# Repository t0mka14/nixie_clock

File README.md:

# nixie_clock
6 digit nixie clock

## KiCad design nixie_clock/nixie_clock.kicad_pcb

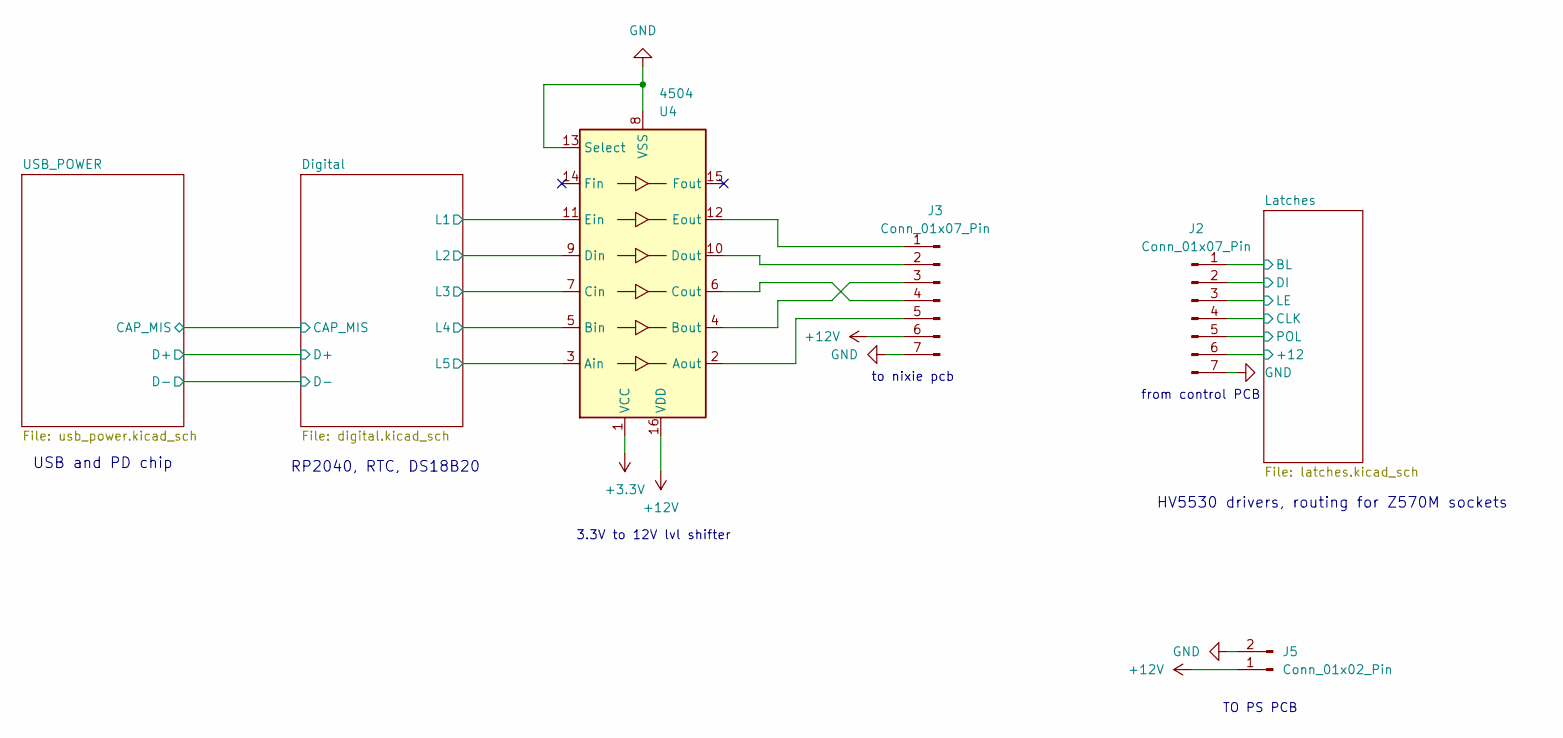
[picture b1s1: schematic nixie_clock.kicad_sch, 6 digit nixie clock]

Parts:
J2, J3: Conn_01x07_Pin; PinHeader_1x07_P2.54mm_Vertical
J5: Conn_01x02_Pin; PinHeader_1x02_P2.54mm_Vertical
U4: 4504; Texas_PDSO_G16

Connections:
+3.3V: U4.1 (VCC); also elsewhere on the board
+12V: J3.6, J5.1, U4.16 (VDD); also elsewhere on the board
/Digital/L1: U4.11 (Ein); also elsewhere on the board
/Digital/L2: U4.9 (Din); also elsewhere on the board
/Digital/L3: U4.7 (Cin); also elsewhere on the board
/Digital/L4: U4.5 (Bin); also elsewhere on the board
/Digital/L5: U4.3 (Ain); also elsewhere on the board
/Latches/+12: J2.6; also elsewhere on the board
/Latches/BL: J2.1; also elsewhere on the board
/Latches/CLK: J2.4; also elsewhere on the board
/Latches/DI: J2.2; also elsewhere on the board
/Latches/LE: J2.3; also elsewhere on the board
/Latches/POL: J2.5; also elsewhere on the board
GND: J2.7, J3.7, J5.2, U4.8 (VSS), U4.13 (Select); also elsewhere on the board
unnamed: J3.1, U4.12 (Eout)
unnamed: J3.2, U4.10 (Dout)
unnamed: J3.3, U4.4 (Bout)
unnamed: J3.4, U4.6 (Cout)
unnamed: J3.5, U4.2 (Aout)

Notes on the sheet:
to nixie pcb
USB and PD chip
TO PS PCB
RP2040, RTC, DS18B20
from control PCB
HV5530 drivers, routing for Z570M sockets
3.3V to 12V lvl shifter

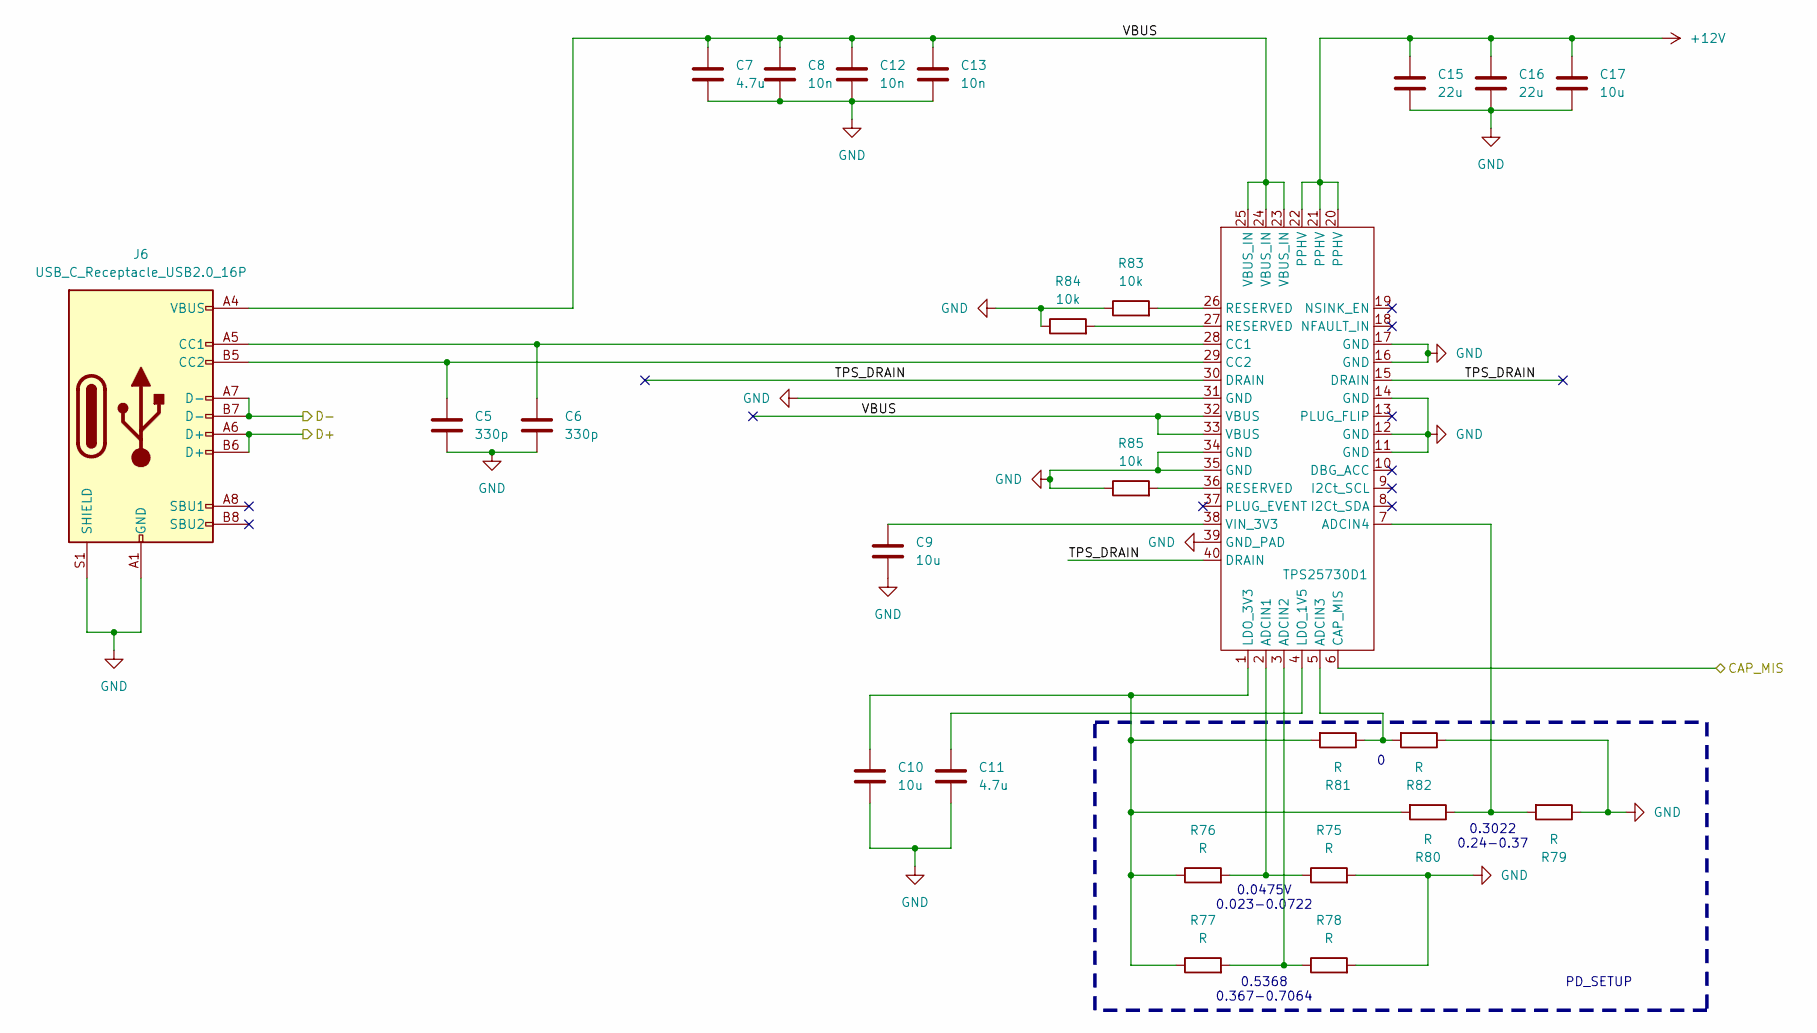
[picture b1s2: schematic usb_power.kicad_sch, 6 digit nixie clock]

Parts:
C5, C6: 330p; C_0603_1608Metric
C7, C11: 4.7u; C_0805_2012Metric
C8, C12, C13: 10n; C_0805_2012Metric
C9, C10, C17: 10u; C_0805_2012Metric
C15, C16: 22u; C_0805_2012Metric
J6: USB_C_Receptacle_USB2.0_16P; Conn_USB_C_Socket_Molex_2171790001
R75, R76, R77, R78, R79, R80, R81, R82: R; R_0805_2012Metric
R83, R84, R85: 10k; R_0805_2012Metric
TPS25730D1: IC_TPS25730D

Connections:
+12V: C15.1, C16.1, C17.1, TPS25730D1.20 (PPHV), TPS25730D1.21 (PPHV), TPS25730D1.22 (PPHV); also elsewhere on the board
/Digital/CAP_MIS: TPS25730D1.6 (CAP_MIS); also elsewhere on the board
/Digital/D+: J6.A6 (D+), J6.B6 (D+); also elsewhere on the board
/Digital/D-: J6.A7 (D-), J6.B7 (D-); also elsewhere on the board
/USB_POWER/TPS_DRAIN: TPS25730D1.15 (DRAIN), TPS25730D1.30 (DRAIN), TPS25730D1.40 (DRAIN)
/USB_POWER/VBUS: C7.1, C8.1, C12.1, C13.1, J6.A4 (VBUS), J6.A9 (VBUS), J6.B4 (VBUS), J6.B9 (VBUS), TPS25730D1.23 (VBUS_IN), TPS25730D1.24 (VBUS_IN), TPS25730D1.25 (VBUS_IN), TPS25730D1.32 (VBUS), TPS25730D1.33 (VBUS)
GND: C5.2, C6.2, C7.2, C8.2, C9.1, C10.2, C11.2, C12.2, C13.2, C15.2, C16.2, C17.2, J6.A1 (GND), J6.A12 (GND), J6.B1 (GND), J6.B12 (GND), J6.S1 (SHIELD), R75.2, R78.2, R79.1, R82.1, R83.1, R84.1, R85.1, TPS25730D1.11 (GND), TPS25730D1.12 (GND), TPS25730D1.14 (GND), TPS25730D1.16 (GND), TPS25730D1.17 (GND), TPS25730D1.31 (GND), TPS25730D1.34 (GND), TPS25730D1.35 (GND), TPS25730D1.39 (GND_PAD); also elsewhere on the board
unnamed: C6.1, J6.A5 (CC1), TPS25730D1.28 (CC1)
unnamed: C5.1, J6.B5 (CC2), TPS25730D1.29 (CC2)
unnamed: R83.2, TPS25730D1.26 (RESERVED)
unnamed: R84.2, TPS25730D1.27 (RESERVED)
unnamed: R85.2, TPS25730D1.36 (RESERVED)
unnamed: R75.1, R76.2, TPS25730D1.2 (ADCIN1)
unnamed: R77.2, R78.1, TPS25730D1.3 (ADCIN2)
unnamed: R81.1, R82.2, TPS25730D1.5 (ADCIN3)
unnamed: R79.2, R80.1, TPS25730D1.7 (ADCIN4)
unnamed: C11.1, TPS25730D1.4 (LDO_1V5)
unnamed: C10.1, R76.1, R77.1, R80.2, R81.2, TPS25730D1.1 (LDO_3V3)
unnamed: C9.2, TPS25730D1.38 (VIN_3V3)

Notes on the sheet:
PD_SETUP
0.5368 0.367-0.7064
0.3022 0.24-0.37
0.0475V 0.023-0.0722

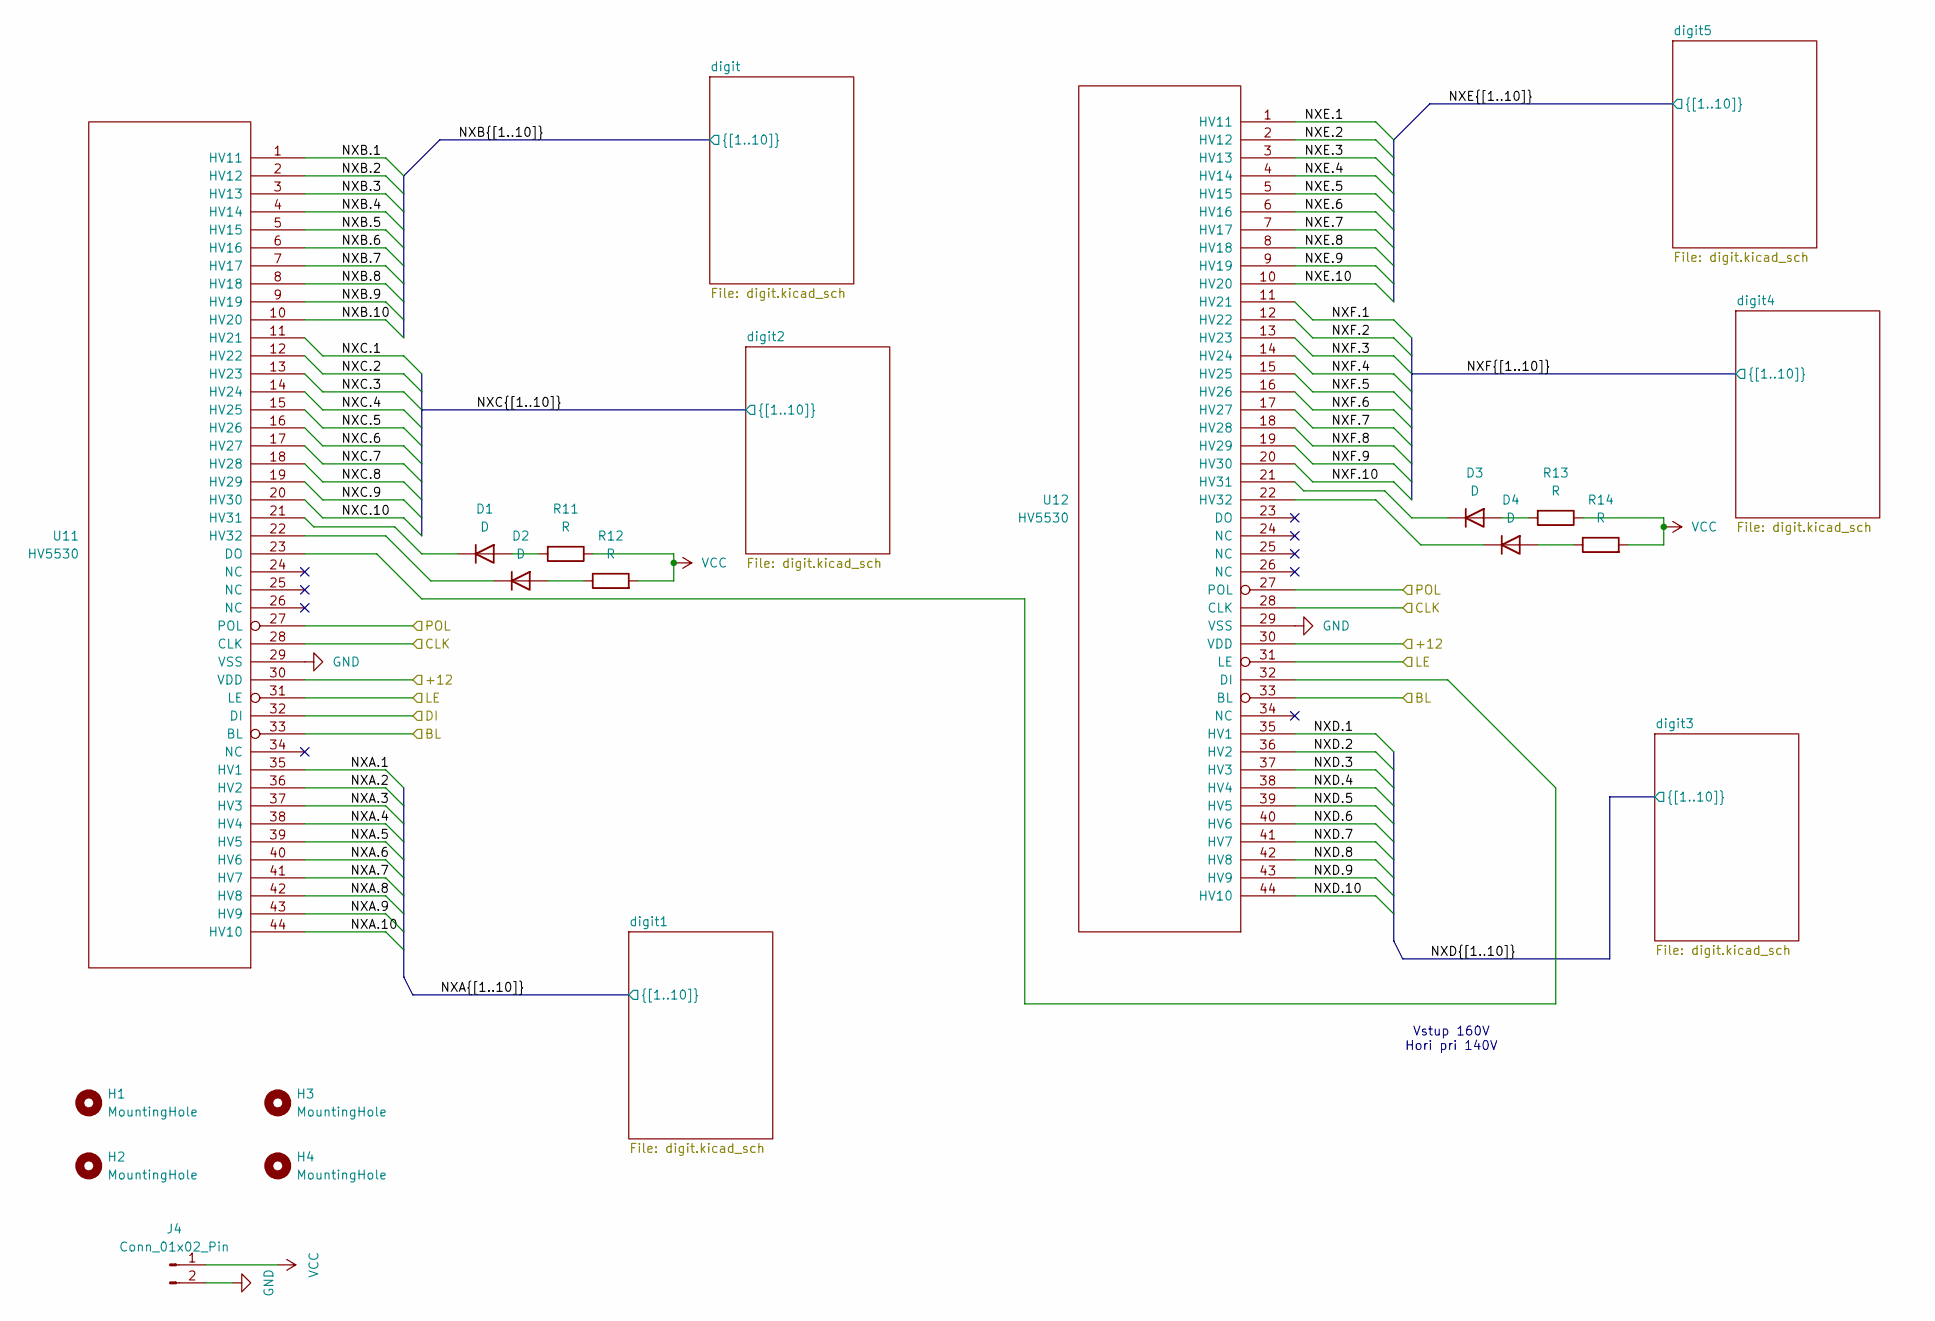
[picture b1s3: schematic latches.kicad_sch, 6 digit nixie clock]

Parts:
D1, D2, D3, D4: D; CP_Radial_D8.0mm_P5.00mm
H1, H2, H3, H4: MountingHole; MountingHole_3.2mm_M3
J4: Conn_01x02_Pin; PhoenixContact_MCV_1,5_2-G-3.5_1x02_P3.50mm_Vertical
R11, R12, R13, R14: R; R_1206_3216Metric
U11, U12: HV5530; PQFP-44_HV5530

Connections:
/Latches/+12: U11.30 (VDD), U12.30 (VDD); also elsewhere on the board
/Latches/BL: U11.33 (BL), U12.33 (BL); also elsewhere on the board
/Latches/CLK: U11.28 (CLK), U12.28 (CLK); also elsewhere on the board
/Latches/DI: U11.32 (DI); also elsewhere on the board
/Latches/LE: U11.31 (LE), U12.31 (LE); also elsewhere on the board
/Latches/NXA.1: U11.35 (HV1); also elsewhere on the board
/Latches/NXA.2: U11.36 (HV2); also elsewhere on the board
/Latches/NXA.3: U11.37 (HV3); also elsewhere on the board
/Latches/NXA.4: U11.38 (HV4); also elsewhere on the board
/Latches/NXA.5: U11.39 (HV5); also elsewhere on the board
/Latches/NXA.6: U11.40 (HV6); also elsewhere on the board
/Latches/NXA.7: U11.41 (HV7); also elsewhere on the board
/Latches/NXA.8: U11.42 (HV8); also elsewhere on the board
/Latches/NXA.9: U11.43 (HV9); also elsewhere on the board
/Latches/NXA.10: U11.44 (HV10); also elsewhere on the board
/Latches/NXB.1: U11.1 (HV11); also elsewhere on the board
/Latches/NXB.2: U11.2 (HV12); also elsewhere on the board
/Latches/NXB.3: U11.3 (HV13); also elsewhere on the board
/Latches/NXB.4: U11.4 (HV14); also elsewhere on the board
/Latches/NXB.5: U11.5 (HV15); also elsewhere on the board
/Latches/NXB.6: U11.6 (HV16); also elsewhere on the board
/Latches/NXB.7: U11.7 (HV17); also elsewhere on the board
/Latches/NXB.8: U11.8 (HV18); also elsewhere on the board
/Latches/NXB.9: U11.9 (HV19); also elsewhere on the board
/Latches/NXB.10: U11.10 (HV20); also elsewhere on the board
/Latches/NXC.1: U11.11 (HV21); also elsewhere on the board
/Latches/NXC.2: U11.12 (HV22); also elsewhere on the board
/Latches/NXC.3: U11.13 (HV23); also elsewhere on the board
/Latches/NXC.4: U11.14 (HV24); also elsewhere on the board
/Latches/NXC.5: U11.15 (HV25); also elsewhere on the board
/Latches/NXC.6: U11.16 (HV26); also elsewhere on the board
/Latches/NXC.7: U11.17 (HV27); also elsewhere on the board
/Latches/NXC.8: U11.18 (HV28); also elsewhere on the board
/Latches/NXC.9: U11.19 (HV29); also elsewhere on the board
/Latches/NXC.10: U11.20 (HV30); also elsewhere on the board
/Latches/NXD.1: U12.35 (HV1); also elsewhere on the board
/Latches/NXD.2: U12.36 (HV2); also elsewhere on the board
/Latches/NXD.3: U12.37 (HV3); also elsewhere on the board
/Latches/NXD.4: U12.38 (HV4); also elsewhere on the board
/Latches/NXD.5: U12.39 (HV5); also elsewhere on the board
/Latches/NXD.6: U12.40 (HV6); also elsewhere on the board
/Latches/NXD.7: U12.41 (HV7); also elsewhere on the board
/Latches/NXD.8: U12.42 (HV8); also elsewhere on the board
/Latches/NXD.9: U12.43 (HV9); also elsewhere on the board
/Latches/NXD.10: U12.44 (HV10); also elsewhere on the board
/Latches/NXE.1: U12.1 (HV11); also elsewhere on the board
/Latches/NXE.2: U12.2 (HV12); also elsewhere on the board
/Latches/NXE.3: U12.3 (HV13); also elsewhere on the board
/Latches/NXE.4: U12.4 (HV14); also elsewhere on the board
/Latches/NXE.5: U12.5 (HV15); also elsewhere on the board
/Latches/NXE.6: U12.6 (HV16); also elsewhere on the board
/Latches/NXE.7: U12.7 (HV17); also elsewhere on the board
/Latches/NXE.8: U12.8 (HV18); also elsewhere on the board
/Latches/NXE.9: U12.9 (HV19); also elsewhere on the board
/Latches/NXE.10: U12.10 (HV20); also elsewhere on the board
/Latches/NXF.1: U12.11 (HV21); also elsewhere on the board
/Latches/NXF.2: U12.12 (HV22); also elsewhere on the board
/Latches/NXF.3: U12.13 (HV23); also elsewhere on the board
/Latches/NXF.4: U12.14 (HV24); also elsewhere on the board
/Latches/NXF.5: U12.15 (HV25); also elsewhere on the board
/Latches/NXF.6: U12.16 (HV26); also elsewhere on the board
/Latches/NXF.7: U12.17 (HV27); also elsewhere on the board
/Latches/NXF.8: U12.18 (HV28); also elsewhere on the board
/Latches/NXF.9: U12.19 (HV29); also elsewhere on the board
/Latches/NXF.10: U12.20 (HV30); also elsewhere on the board
/Latches/POL: U11.27 (POL), U12.27 (POL); also elsewhere on the board
GND: J4.2, U11.29 (VSS), U12.29 (VSS); also elsewhere on the board
unnamed: D1.2 (A), R11.2
unnamed: D1.1 (K), U11.21 (HV31)
unnamed: D2.2 (A), R12.1
unnamed: D2.1 (K), U11.22 (HV32)
unnamed: D3.2 (A), R13.2
unnamed: D3.1 (K), U12.21 (HV31)
unnamed: D4.2 (A), R14.1
unnamed: D4.1 (K), U12.22 (HV32)
unnamed: U11.23 (DO), U12.32 (DI)
VCC: J4.1, R11.1, R12.2, R13.1, R14.2; also elsewhere on the board

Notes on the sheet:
Vstup 160V Hori pri 140V

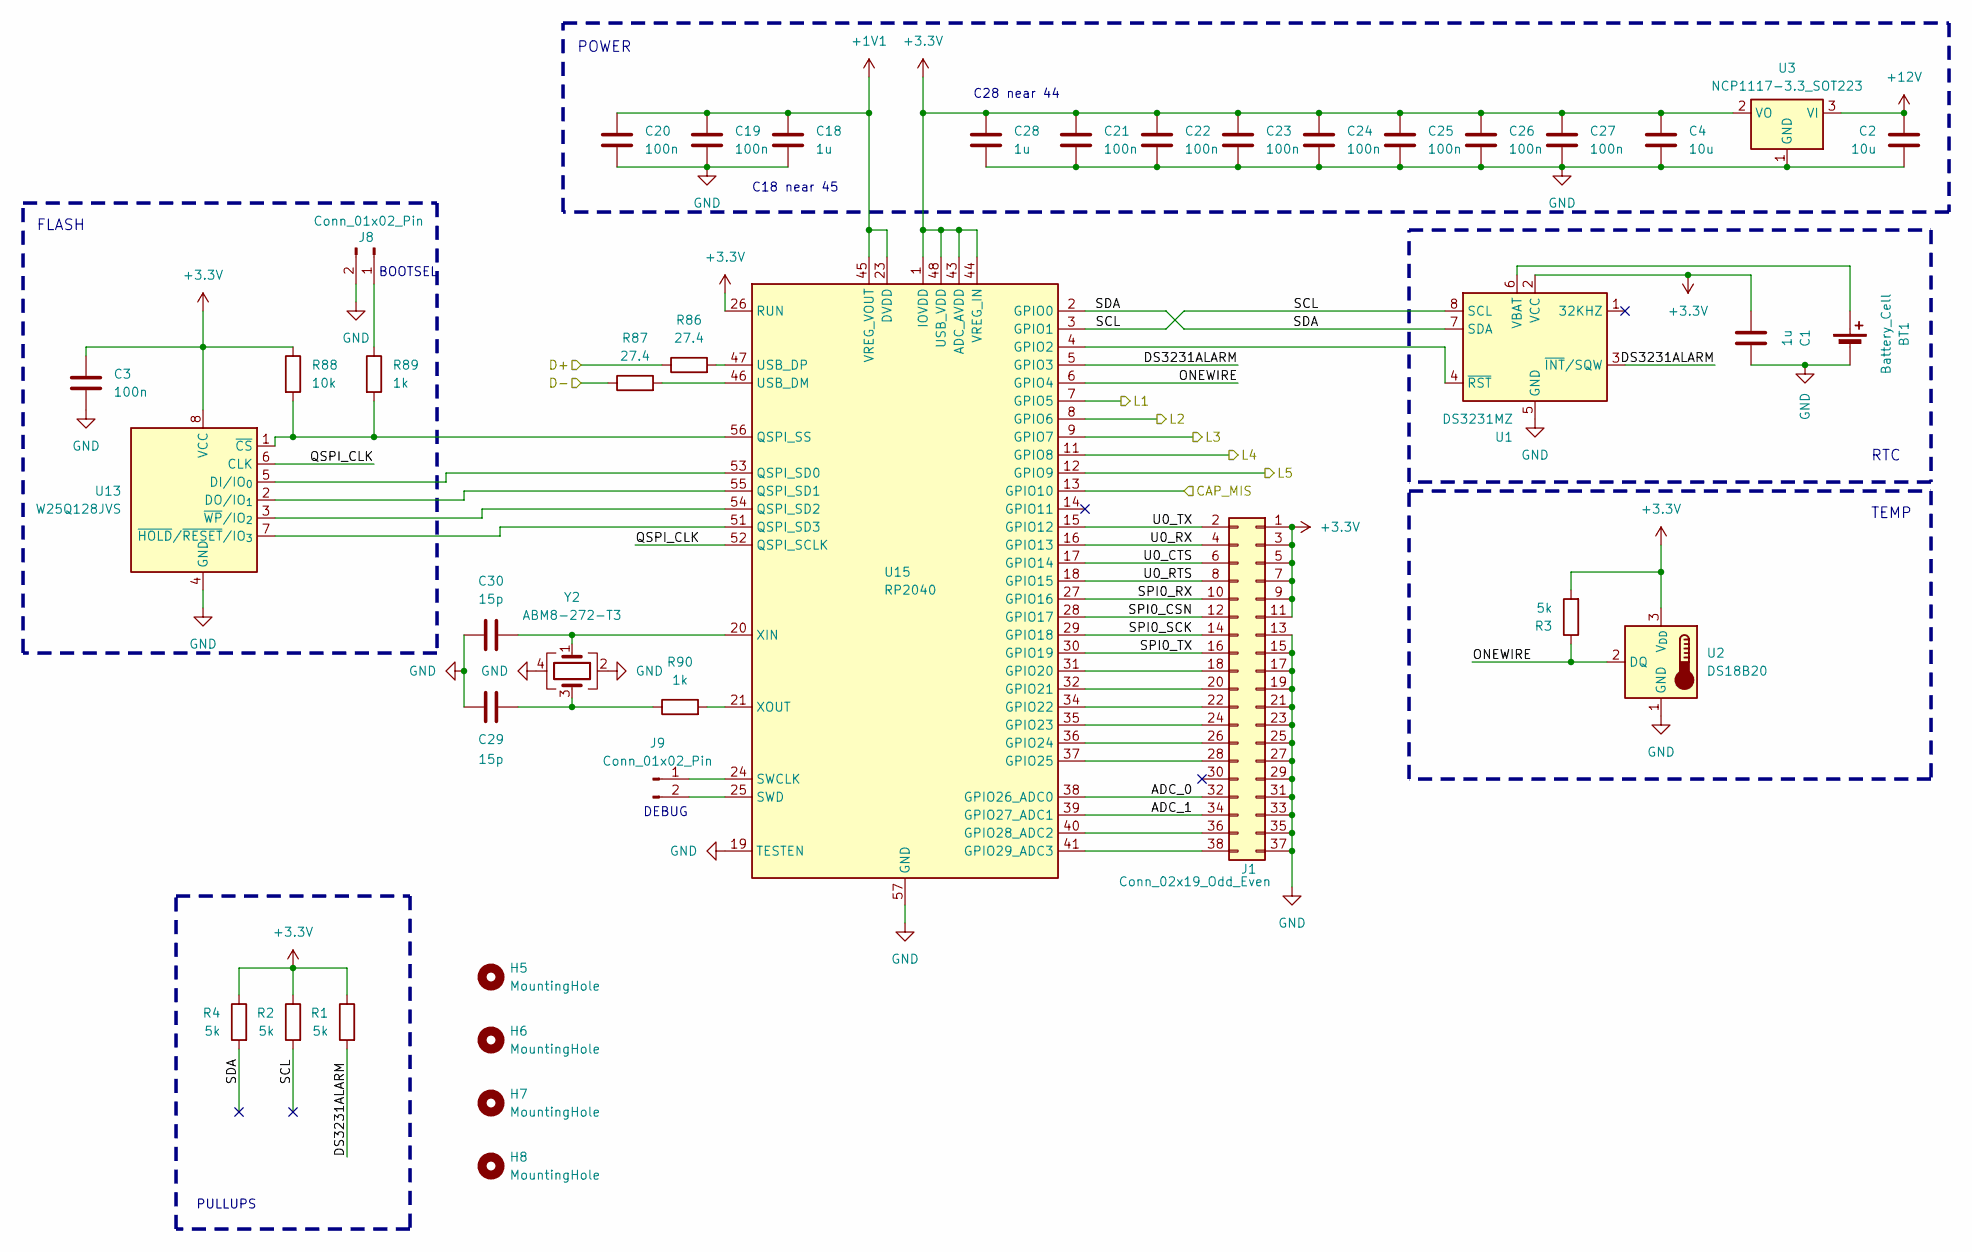
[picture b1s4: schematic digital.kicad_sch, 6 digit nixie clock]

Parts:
BT1: Battery_Cell; Battery_Panasonic_CR2032-HFN_Horizontal_CircularHoles
C1: 1u; C_0805_2012Metric
C2, C4: 10u; C_0805_2012Metric
C3, C19, C20, C21, C22, C23, C24, C25, C26, C27: 100n; C_0603_1608Metric
C18, C28: 1u; C_0603_1608Metric
C29, C30: 15p; C_0603_1608Metric
H5, H6, H7, H8: MountingHole; MountingHole_3.2mm_M3
J1: Conn_02x19_Odd_Even; PinHeader_2x19_P2.54mm_Vertical
J8, J9: Conn_01x02_Pin; PinHeader_1x02_P2.54mm_Vertical
R1, R2, R3, R4: 5k; R_0805_2012Metric
R86, R87: 27.4; R_0603_1608Metric
R88: 10k; R_0603_1608Metric
R89, R90: 1k; R_0603_1608Metric
U1: DS3231MZ; SOIC-8_3.9x4.9mm_P1.27mm
U2: DS18B20; TO-92_Inline
U3: NCP1117-3.3_SOT223; SOT-223-3_TabPin2
U13: W25Q128JVS; SOIC-8_5.3x5.3mm_P1.27mm
U15: RP2040; QFN-56-1EP_7x7mm_P0.4mm_EP3.2x3.2mm
Y2: ABM8-272-T3

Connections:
+1V1: C18.1, C19.1, C20.1, U15.23 (DVDD), U15.45 (VREG_VOUT), U15.50 (DVDD)
+3.3V: C1.2, C3.1, C4.1, C21.1, C22.1, C23.1, C24.1, C25.1, C26.1, C27.1, C28.1, J1.1, J1.3, J1.5, J1.7, J1.9, J1.11, R1.1, R2.1, R3.2, R4.1, R88.1, U1.2 (VCC), U2.3 (V_{DD}), U3.2 (VO), U13.8 (VCC), U15.1 (IOVDD), U15.10 (IOVDD), U15.22 (IOVDD), U15.26 (RUN), U15.33 (IOVDD), U15.42 (IOVDD), U15.43 (ADC_AVDD), U15.44 (VREG_IN), U15.48 (USB_VDD), U15.49 (IOVDD); also elsewhere on the board
+12V: C2.1, U3.3 (VI); also elsewhere on the board
/Digital/ADC_0: J1.32, U15.38 (GPIO26_ADC0)
/Digital/ADC_1: J1.34, U15.39 (GPIO27_ADC1)
/Digital/CAP_MIS: U15.13 (GPIO10); also elsewhere on the board
/Digital/D+: R86.1; also elsewhere on the board
/Digital/D-: R87.1; also elsewhere on the board
/Digital/DS3231ALARM: R1.2, U1.3 (~INT/SQW), U15.5 (GPIO3)
/Digital/L1: U15.7 (GPIO5); also elsewhere on the board
/Digital/L2: U15.8 (GPIO6); also elsewhere on the board
/Digital/L3: U15.9 (GPIO7); also elsewhere on the board
/Digital/L4: U15.11 (GPIO8); also elsewhere on the board
/Digital/L5: U15.12 (GPIO9); also elsewhere on the board
/Digital/ONEWIRE: R3.1, U2.2 (DQ), U15.6 (GPIO4)
/Digital/QSPI_CLK: U13.6 (CLK), U15.52 (QSPI_SCLK)
/Digital/SCL: R2.2, U1.8 (SCL), U15.3 (GPIO1)
/Digital/SDA: R4.2, U1.7 (SDA), U15.2 (GPIO0)
/Digital/SPI0_CSN: J1.12, U15.28 (GPIO17)
/Digital/SPI0_RX: J1.10, U15.27 (GPIO16)
/Digital/SPI0_SCK: J1.14, U15.29 (GPIO18)
/Digital/SPI0_TX: J1.16, U15.30 (GPIO19)
/Digital/U0_CTS: J1.6, U15.17 (GPIO14)
/Digital/U0_RTS: J1.8, U15.18 (GPIO15)
/Digital/U0_RX: J1.4, U15.16 (GPIO13)
/Digital/U0_TX: J1.2, U15.15 (GPIO12)
GND: BT1.2 (-), C1.1, C2.2, C3.2, C4.2, C18.2, C19.2, C20.2, C21.2, C22.2, C23.2, C24.2, C25.2, C26.2, C27.2, C28.2, C29.1, C30.1, J1.13, J1.15, J1.17, J1.19, J1.21, J1.23, J1.25, J1.27, J1.29, J1.31, J1.33, J1.35, J1.37, J8.2, U1.5 (GND), U2.1 (GND), U3.1 (GND), U13.4 (GND), U15.19 (TESTEN), U15.57 (GND), Y2.2, Y2.4; also elsewhere on the board
unnamed: BT1.1 (+), U1.6 (VBAT)
unnamed: C29.2, R90.1, Y2.3
unnamed: J1.18, U15.31 (GPIO20)
unnamed: J1.20, U15.32 (GPIO21)
unnamed: J1.22, U15.34 (GPIO22)
unnamed: J1.24, U15.35 (GPIO23)
unnamed: J1.26, U15.36 (GPIO24)
unnamed: J1.28, U15.37 (GPIO25)
unnamed: J1.36, U15.40 (GPIO28_ADC2)
unnamed: J1.38, U15.41 (GPIO29_ADC3)
unnamed: J8.1, R89.1
unnamed: J9.1, U15.24 (SWCLK)
unnamed: J9.2, U15.25 (SWD)
unnamed: U1.4 (~RST), U15.4 (GPIO2)
unnamed: U13.5 (DI/IO_{0}), U15.53 (QSPI_SD0)
unnamed: U13.2 (DO/IO_{1}), U15.55 (QSPI_SD1)
unnamed: R88.2, R89.2, U13.1 (~CS), U15.56 (QSPI_SS)
unnamed: U13.7 (~HOLD/~RESET/IO_{3}), U15.51 (QSPI_SD3)
unnamed: U13.3 (~WP/IO_{2}), U15.54 (QSPI_SD2)
unnamed: R87.2, U15.46 (USB_DM)
unnamed: R86.2, U15.47 (USB_DP)
unnamed: C30.2, U15.20 (XIN), Y2.1
unnamed: R90.2, U15.21 (XOUT)

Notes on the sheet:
BOOTSEL
RTC
PULLUPS
C28 near 44
C18 near 45
FLASH
TEMP
DEBUG
POWER

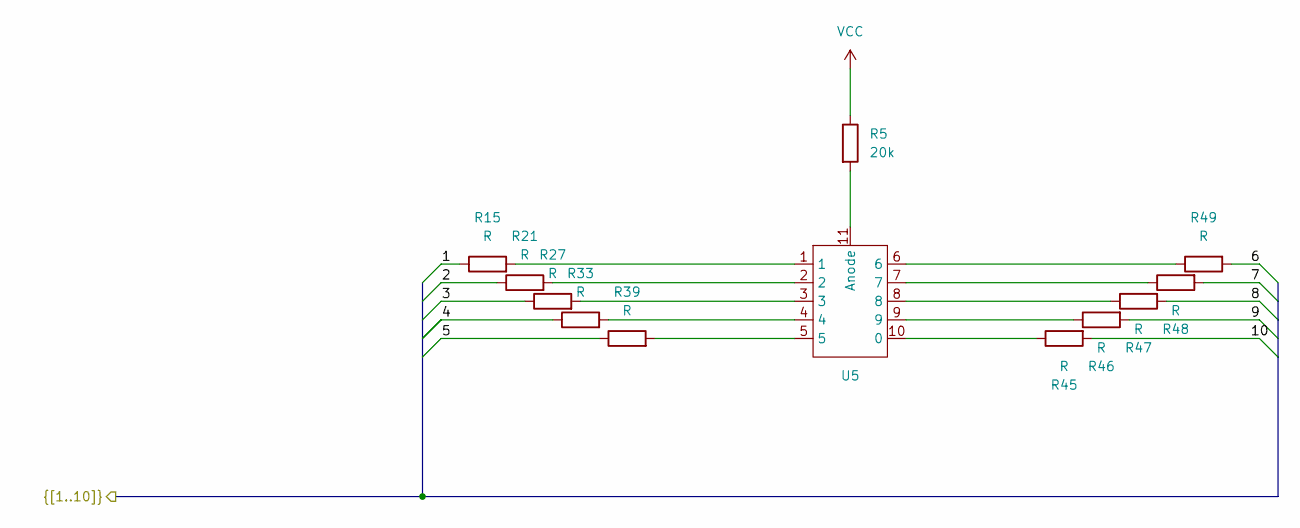
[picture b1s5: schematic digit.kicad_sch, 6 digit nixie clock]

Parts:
R5: 20k; R_1206_3216Metric
R15, R21, R27, R33, R39, R45, R46, R47, R48, R49: R; R_0805_2012Metric
U5: Z570M_patice

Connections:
/Latches/NXB.1: R15.1; also elsewhere on the board
/Latches/NXB.2: R21.1; also elsewhere on the board
/Latches/NXB.3: R27.1; also elsewhere on the board
/Latches/NXB.4: R33.1; also elsewhere on the board
/Latches/NXB.5: R39.1; also elsewhere on the board
/Latches/NXB.6: R49.2; also elsewhere on the board
/Latches/NXB.7: R48.2; also elsewhere on the board
/Latches/NXB.8: R47.2; also elsewhere on the board
/Latches/NXB.9: R46.2; also elsewhere on the board
/Latches/NXB.10: R45.2; also elsewhere on the board
unnamed: R15.2, U5.1
unnamed: R21.2, U5.2
unnamed: R27.2, U5.3
unnamed: R33.2, U5.4
unnamed: R39.2, U5.5
unnamed: R46.1, U5.9
unnamed: R47.1, U5.8
unnamed: R48.1, U5.7
unnamed: R49.1, U5.6
unnamed: R45.1, U5.10 (0)
unnamed: R5.2, U5.11 (Anode)
VCC: R5.1; also elsewhere on the board

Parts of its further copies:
R6, R7, R8, R9, R10: 20k; R_1206_3216Metric
R16, R17, R18, R19, R20, R22, R23, R24, R25, R26, R28, R29, R30, R31, R32, R34, R35, R36, R37, R38, R40, R41, R42, R43, R44, R50, R51, R52, R53, R54, R55, R56, R57, R58, R59, R60, R61, R62, R63, R64, R65, R66, R67, R68, R69, R70, R71, R72, R73, R74: R; R_0805_2012Metric
U6, U7, U8, U9, U10: Z570M_patice

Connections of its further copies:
/Latches/NXA.1: R16.1; also elsewhere on the board
/Latches/NXA.2: R22.1; also elsewhere on the board
/Latches/NXA.3: R28.1; also elsewhere on the board
/Latches/NXA.4: R34.1; also elsewhere on the board
/Latches/NXA.5: R40.1; also elsewhere on the board
/Latches/NXA.6: R54.2; also elsewhere on the board
/Latches/NXA.7: R53.2; also elsewhere on the board
/Latches/NXA.8: R52.2; also elsewhere on the board
/Latches/NXA.9: R51.2; also elsewhere on the board
/Latches/NXA.10: R50.2; also elsewhere on the board
/Latches/NXC.1: R17.1; also elsewhere on the board
/Latches/NXC.2: R23.1; also elsewhere on the board
/Latches/NXC.3: R29.1; also elsewhere on the board
/Latches/NXC.4: R35.1; also elsewhere on the board
/Latches/NXC.5: R41.1; also elsewhere on the board
/Latches/NXC.6: R59.2; also elsewhere on the board
/Latches/NXC.7: R58.2; also elsewhere on the board
/Latches/NXC.8: R57.2; also elsewhere on the board
/Latches/NXC.9: R56.2; also elsewhere on the board
/Latches/NXC.10: R55.2; also elsewhere on the board
/Latches/NXD.1: R18.1; also elsewhere on the board
/Latches/NXD.2: R24.1; also elsewhere on the board
/Latches/NXD.3: R30.1; also elsewhere on the board
/Latches/NXD.4: R36.1; also elsewhere on the board
/Latches/NXD.5: R42.1; also elsewhere on the board
/Latches/NXD.6: R64.2; also elsewhere on the board
/Latches/NXD.7: R63.2; also elsewhere on the board
/Latches/NXD.8: R62.2; also elsewhere on the board
/Latches/NXD.9: R61.2; also elsewhere on the board
/Latches/NXD.10: R60.2; also elsewhere on the board
/Latches/NXE.1: R20.1; also elsewhere on the board
/Latches/NXE.2: R26.1; also elsewhere on the board
/Latches/NXE.3: R32.1; also elsewhere on the board
/Latches/NXE.4: R38.1; also elsewhere on the board
/Latches/NXE.5: R44.1; also elsewhere on the board
/Latches/NXE.6: R74.2; also elsewhere on the board
/Latches/NXE.7: R73.2; also elsewhere on the board
/Latches/NXE.8: R72.2; also elsewhere on the board
/Latches/NXE.9: R71.2; also elsewhere on the board
/Latches/NXE.10: R70.2; also elsewhere on the board
/Latches/NXF.1: R19.1; also elsewhere on the board
/Latches/NXF.2: R25.1; also elsewhere on the board
/Latches/NXF.3: R31.1; also elsewhere on the board
/Latches/NXF.4: R37.1; also elsewhere on the board
/Latches/NXF.5: R43.1; also elsewhere on the board
/Latches/NXF.6: R69.2; also elsewhere on the board
/Latches/NXF.7: R68.2; also elsewhere on the board
/Latches/NXF.8: R67.2; also elsewhere on the board
/Latches/NXF.9: R66.2; also elsewhere on the board
/Latches/NXF.10: R65.2; also elsewhere on the board
unnamed: R16.2, U6.1
unnamed: R17.2, U7.1
unnamed: R18.2, U8.1
unnamed: R19.2, U9.1
unnamed: R20.2, U10.1
unnamed: R22.2, U6.2
unnamed: R23.2, U7.2
unnamed: R24.2, U8.2
unnamed: R25.2, U9.2
unnamed: R26.2, U10.2
unnamed: R28.2, U6.3
unnamed: R29.2, U7.3
unnamed: R30.2, U8.3
unnamed: R31.2, U9.3
unnamed: R32.2, U10.3
unnamed: R34.2, U6.4
unnamed: R35.2, U7.4
unnamed: R36.2, U8.4
unnamed: R37.2, U9.4
unnamed: R38.2, U10.4
unnamed: R40.2, U6.5
unnamed: R41.2, U7.5
unnamed: R42.2, U8.5
unnamed: R43.2, U9.5
unnamed: R44.2, U10.5
unnamed: R51.1, U6.9
unnamed: R52.1, U6.8
unnamed: R53.1, U6.7
unnamed: R54.1, U6.6
unnamed: R56.1, U7.9
unnamed: R57.1, U7.8
unnamed: R58.1, U7.7
unnamed: R59.1, U7.6
unnamed: R61.1, U8.9
unnamed: R62.1, U8.8
unnamed: R63.1, U8.7
unnamed: R64.1, U8.6
unnamed: R66.1, U9.9
unnamed: R67.1, U9.8
unnamed: R68.1, U9.7
unnamed: R69.1, U9.6
unnamed: R71.1, U10.9
unnamed: R72.1, U10.8
unnamed: R73.1, U10.7
unnamed: R74.1, U10.6
unnamed: R50.1, U6.10 (0)
unnamed: R6.2, U6.11 (Anode)
unnamed: R55.1, U7.10 (0)
unnamed: R7.2, U7.11 (Anode)
unnamed: R60.1, U8.10 (0)
unnamed: R8.2, U8.11 (Anode)
unnamed: R65.1, U9.10 (0)
unnamed: R9.2, U9.11 (Anode)
unnamed: R70.1, U10.10 (0)
unnamed: R10.2, U10.11 (Anode)
VCC: R6.1, R7.1, R8.1, R9.1, R10.1; also elsewhere on the board

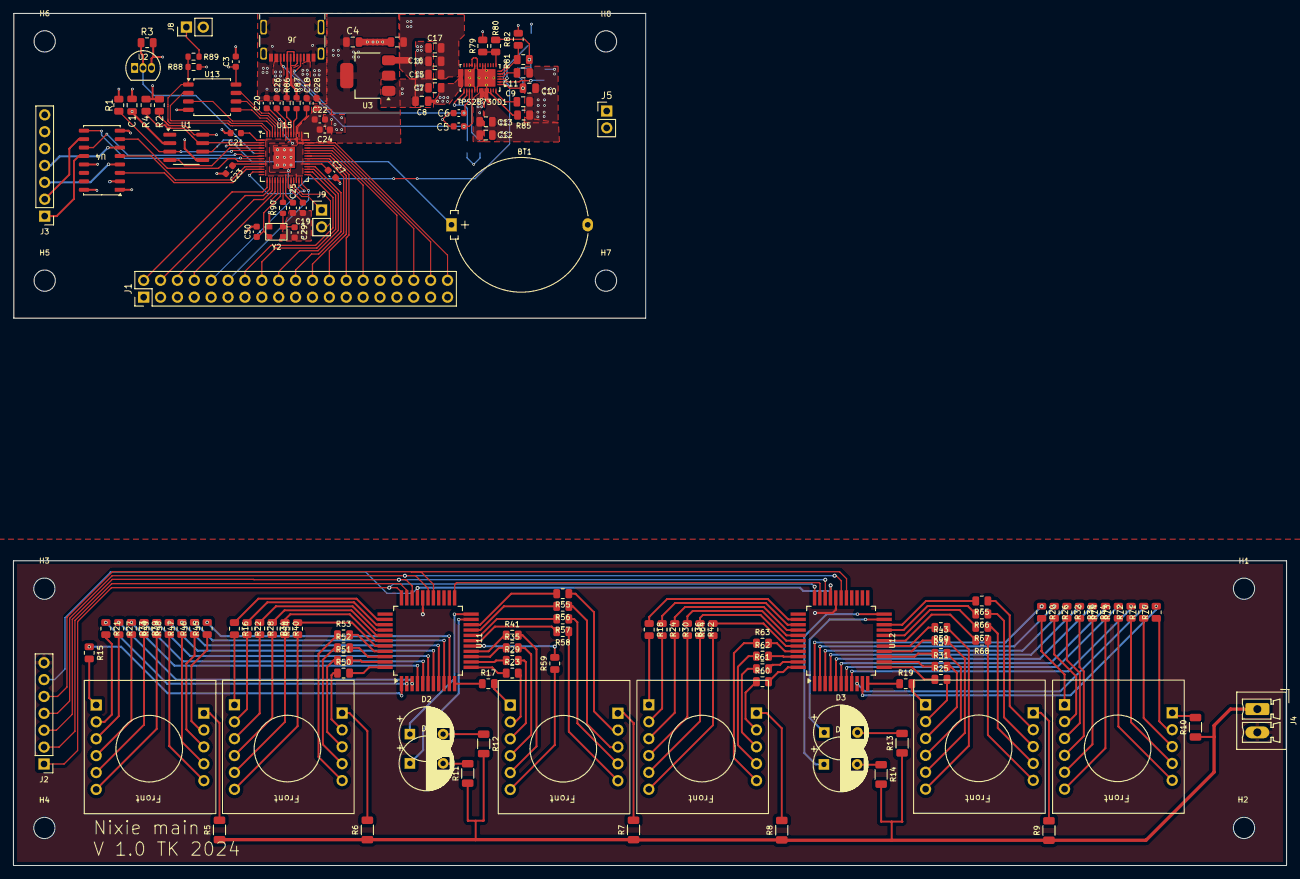
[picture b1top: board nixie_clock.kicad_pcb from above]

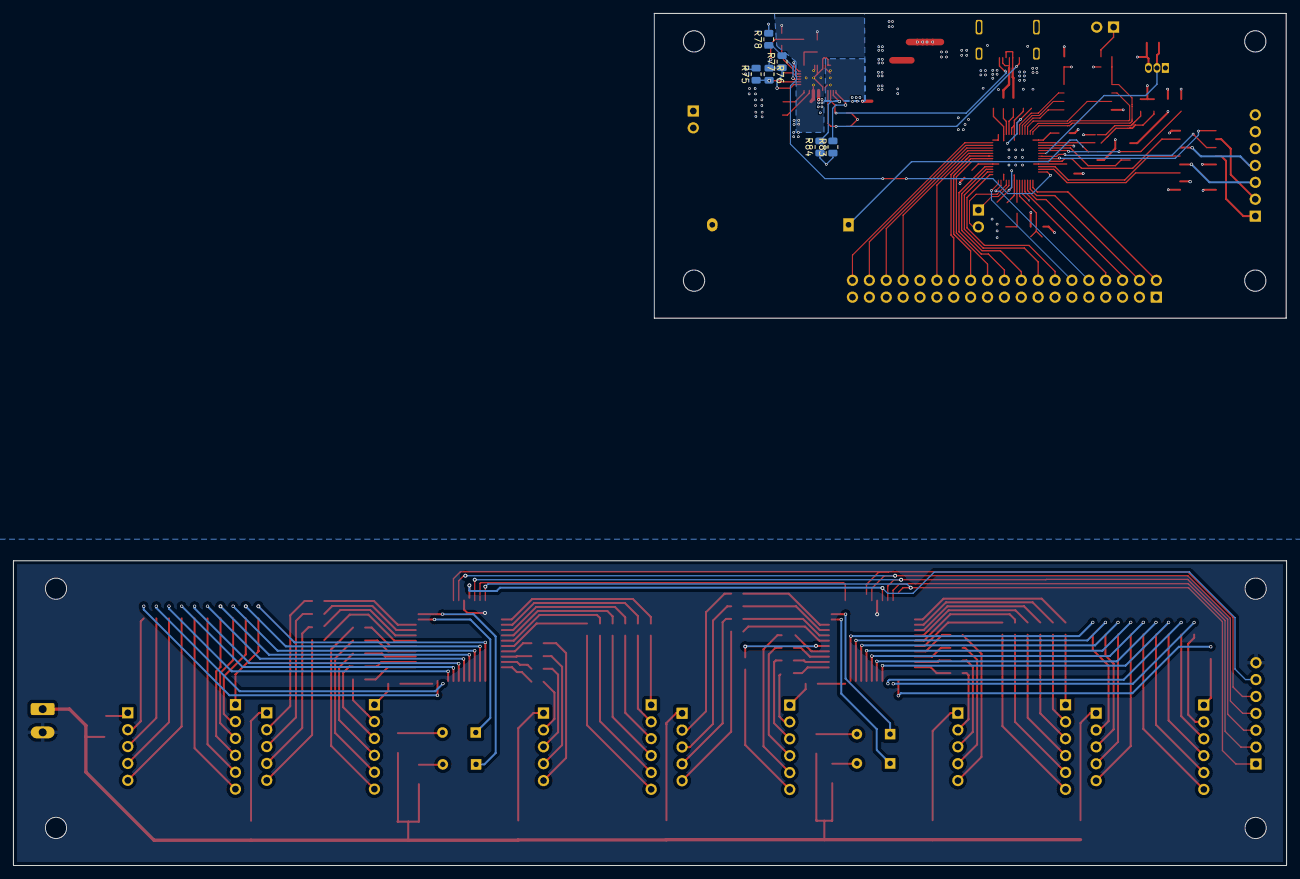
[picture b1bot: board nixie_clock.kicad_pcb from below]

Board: 4 copper layers, 191.6 x 128.2 mm, 156 parts (6 on the bottom side), 211 nets.

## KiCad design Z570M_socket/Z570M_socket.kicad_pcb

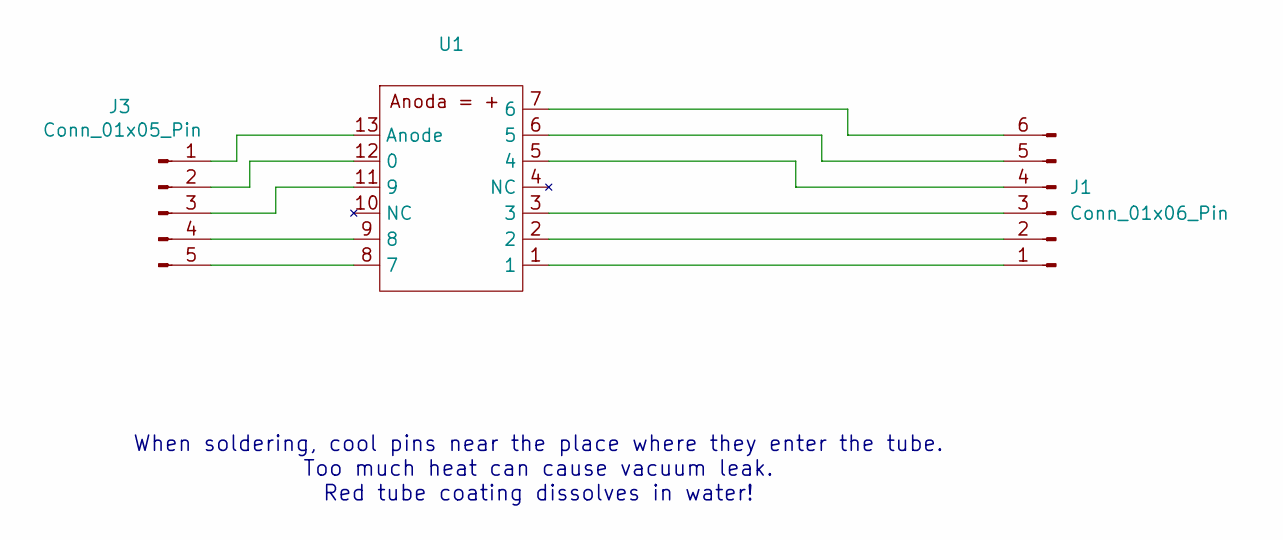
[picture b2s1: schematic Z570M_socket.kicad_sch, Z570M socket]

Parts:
J1: Conn_01x06_Pin; PinHeader_1x06_P2.54mm_Vertical
J3: Conn_01x05_Pin; PinHeader_1x05_P2.54mm_Vertical
U1: Z570M

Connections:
unnamed: J1.1, U1.1
unnamed: J1.2, U1.2
unnamed: J1.3, U1.3
unnamed: J1.4, U1.5 (4)
unnamed: J1.5, U1.6 (5)
unnamed: J1.6, U1.7 (6)
unnamed: J3.1, U1.13 (Anode)
unnamed: J3.2, U1.12 (0)
unnamed: J3.3, U1.11 (9)
unnamed: J3.4, U1.9 (8)
unnamed: J3.5, U1.8 (7)

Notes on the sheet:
When soldering, cool pins near the place where they enter the tube. Too much heat can cause vacuum leak. Red tube coating dissolves in water!

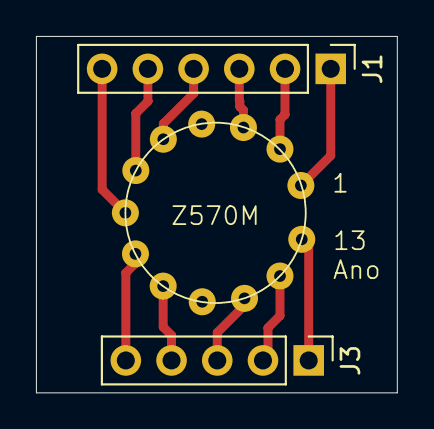
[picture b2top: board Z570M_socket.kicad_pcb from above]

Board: 2 copper layers, 20.1 x 19.8 mm, 3 parts (0 on the bottom side), 11 nets.
